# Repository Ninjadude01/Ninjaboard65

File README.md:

# Ninjaboard65

The Ninjaboard65 is a 65% custom keyboard with a knob! Features include hot-swappable gateron yellow switches, pbt double-shot keycaps, and a 3d printed case + plate. It uses qmk firmware, which is fully customizable so you can assign each key to whatever function you want. I decided to build this project as I love hardware and am already familiar with the basics. I wanted a project that would challenge me, which is why I decided to make my own keyboard. Another reason why is because I love playing video games in my free time, so being able to create my very own input device means alot to me, and would be very useful as I can customize it specifically to meet my gaming needs.

Youtube Video Link: https://www.youtube.com/watch?v=n-olJ9K8aAI

# Zine!
.png)

# IRL Photos vs the 3D Renders

<br>
<br>
<br>

<br>
<br>
<br>

# Layout 
I chose a 65% layout as I like to game in my freetime, and this layout is a perfect mix between everyday functionality while still being small and compact.

# Schematic
I designed the Schematic and PCB in Kicad, and chose to use a raspberry pi pico because it has many GPIO pins, making it perfect for my project as I needed 22 pins for my matrix + rotary encoder to work.

# PCB
I am very proud of my clean wiring, as it took me countless hours and I re-did it many times. I also added some cool designs to the backside silkscreen to add some unique flair to my project!

# Case
My keyboard case was created in fusion, and comes in 3 parts. The main part of the case is the base, and has 3 small PCB supports located near the centre left, centre right, and spacebar area. It will have 5 m2 heatset inserts located around the edge of the base. 

My case uses 5 m2 4mm screws that will screw from the top plate into the base. 

The final part of my case is the pico cover, which covers the microcontroller. It connects to the plate through a snap-fit type mechanism (theres an extruded outline on the plate, and an indented section on the underside of the cover.)

# Assembly Guide 
1. Solder the 1N4148 and Kailh hot-swap sockets to the underside of the pcb.
2. Attach and mount the stabilizers, and solder the rotary encoder onto the pcb (facing upwards).
3. Grab all the Gateron Switches and snap them onto the plate, and flip the plate upside down. 
4. Now, with the plate and your pcb facing downwards, slowly lower the pcb into the plate until all the switches have entered their sockets. 
5. Use a soldering iron to heat up the m2 heatset inserts, and push them into the 5 designated holes in the walls of the base case. 
7. Flip your plate attached the the pcb over, and lower it into the base case.
8. Screw the m2 screws into the holes, cover the open Raspberry Pi Pico with the nameplate (optional), and place the keycaps onto the respective keys.
9. All thats left to do now is to flash your Ninjaboard65!

# Firmware Flashing Steps
1. Download the .uf2 file found in the Firmware Folder.
2. Hold down the BOOTSEL button found on the Pico, and connect it back into your device using a usb cable while holding it.
3. A usb drive called RPI-RP2 will appear on your computer.
4. Drag and drop the .uf2 file onto the drive. 
5. The Pico will automatically reboot and you should be good to go.
6. Enjoy your new Ninjaboard65!

# BOM

|Item|Part Name         |Quantity|Description                    |Cost (USD)|Link                                                                                                                                                                                                                                                                                                                                                                                                                                                                                                                                                                                                                                                                                                                                                                                         |
|----|------------------|--------|-------------------------------|----------|---------------------------------------------------------------------------------------------------------------------------------------------------------------------------------------------------------------------------------------------------------------------------------------------------------------------------------------------------------------------------------------------------------------------------------------------------------------------------------------------------------------------------------------------------------------------------------------------------------------------------------------------------------------------------------------------------------------------------------------------------------------------------------------------|
|1   |Custom PCB        |5       |Printed Circut Board           |$20       |https://jlcpcb.com/                                                                                                                                                                                                                                                                                                                                                                                                                                                                                                                                                                                                                                                                                                                                                                          |
|2   |Kb Switches       |110     |Input                          |$32.05    |https://www.aliexpress.com/item/1005008397216226.html?spm=a2g0o.order_list.order_list_main.28.6a7d1802895Pzz                                                                                                                                                                                                                                                                                                                                                                                                                                                                                                                                                                                                                                                                                 |
|3   |Keycaps (Blue)    |133     |Protection                     |$13.64    |https://www.aliexpress.com/item/1005009580866548.html?spm=a2g0o.order_list.order_list_main.17.6a7d1802895Pzz#nav-specification                                                                                                                                                                                                                                                                                                                                                                                                                                                                                                                                                                                                                                                               |
|4   |Hot-swap Sockets  |110     |Allows hot-swapping of switches|$9.88     |https://www.aliexpress.com/item/1005007232040760.html?spm=a2g0o.order_list.order_list_main.5.6a7d1802895Pzz                                                                                                                                                                                                                                                                                                                                                                                                                                                                                                                                                                                                                                                                                  |
|5   |Rotary Encoder    |1       |You can rotate it              |$3.50     |https://www.digikey.ca/en/products/detail/alps-alpine/EC11E15244B2/19529170                                                                                                                                                                                                                                                                                                                                                                                                                                                                                                                                                                                                                                                                                                                  |
|6   |Encoder Knob cap  |1       |Protection                     |$4.25     |https://www.aliexpress.com/item/1005006531154080.html?spm=a2g0o.order_list.order_list_main.5.256d1802T4w9tK                                                                                                                                                                                                                                                                                                                                                                                                                                                                                                                                                                                                                                                                                  |
|7   |Raspberry pi pico |1       |Microcontroller                |$2.89     |https://www.digikey.ca/en/products/detail/raspberry-pi/SC0915/13684020                                                                                                                                                                                                                                                                                                                                                                                                                                                                                                                                                                                                                                                                                                                       |
|8   |Stabilizers       |8       |Increase steadiness of keys    |$7.86     |https://www.aliexpress.com/item/1005007236845004.html?spm=a2g0o.cart.0.0.722238daCCs9vH&mp=1&pdp_npi=6%40dis%21CAD%21CAD%2010.78%21CAD%2010.78%21%21CAD%2010.78%21%21%21%40210328c017745464960958122e1f40%2112000039909995531%21ct%21CA%217451194651%21%211%210%21                                                                                                                                                                                                                                                                                                                                                                                                                                                                                                                           |
|9   |Rubber Bumpers    |10      |Prevent sliding                |$3.78     |https://www.aliexpress.com/item/1005003881918836.html?spm=a2g0o.productlist.main.26.276a2cb9RSUSKP&algo_pvid=2cb2056c-1932-4d95-a10e-0f118e3ed9cb&algo_exp_id=2cb2056c-1932-4d95-a10e-0f118e3ed9cb-25&pdp                                                                                                                                                                                                                                                                                                                                                                                                                                                                                                                                                                                    |
|10  |M2 Heatset Inserts|100     |Threaded metal hole for screws |$5.76     |https://www.aliexpress.com/item/1005006838108683.html?spm=a2g0o.cart.0.0.1c1b38dalGfMuU&mp=1&pdp_npi=6%40dis%21CAD%21CAD%205.20%21CAD%205.20%21%21CAD%205.20%21%21%21%4021033d9d17760010503013922ef23d%2112000038467725083%21ct%21CA%217451194651%21%211%210%21                                                                                                                                                                                                                                                                                                                                                                                                                                                                                                                              |
|11  |M2 Screw 4mm      |50      |Screw                          |$1.70     |https://www.aliexpress.com/item/32973784147.html?spm=a2g0o.productlist.main.1.304apnmvpnmvhX&algo_pvid=8e4bcfb2-c0a1-48f2-ad5e-84593aa7934a&algo_exp_id=8e4bcfb2-c0a1-48f2-ad5e-84593aa7934a-0&pdp_ext_f=%7B%22order%22%3A%227855%22%2C%22spu_best_type%22%3A%22price%22%2C%22eval%22%3A%221%22%2C%22fromPage%22%3A%22search%22%7D&pdp_npi=6%40dis%21CAD%212.26%212.26%21%21%211.60%211.60%21%402101e2b417760020144634724ef5ec%2112000024189797294%21sea%21CA%217451194651%21X%211%210%21n_tag%3A-29912%3Bd%3A8fd05d1b%3Bm03_new_user%3A-29895&curPageLogUid=kvh1vbqAtJaq&utparam-url=scene%3Asearch%7Cquery_from%3A%7Cx_object_id%3A32973784147%7C_p_origin_prod%3A                                                                                                                         |
|12  |1N4148 Diodes     |100     |Prevent kb switch ghosting     |$1.73     |https://www.aliexpress.com/item/1005004962400215.html?spm=a2g0o.productlist.main.8.314c7Zzp7Zzp1O&aem_p4p_detail=202604120710367250743856096580001658181&algo_pvid=9a5c0ddc-1bdb-4d52-bd69-b6aeb1a7dc6b&algo_exp_id=9a5c0ddc-1bdb-4d52-bd69-b6aeb1a7dc6b-7&pdp_ext_f=%7B%22order%22%3A%222280%22%2C%22spu_best_type%22%3A%22price%22%2C%22eval%22%3A%221%22%2C%22fromPage%22%3A%22search%22%7D&pdp_npi=6%40dis%21CAD%212.39%212.39%21%21%211.69%211.69%21%402101e83017760030363003545e4ed8%2112000031168735020%21sea%21CA%217451194651%21X%211%210%21n_tag%3A-29912%3Bd%3A8fd05d1b%3Bm03_new_user%3A-29895&curPageLogUid=O5tBJUtwCY0i&utparam-url=scene%3Asearch%7Cquery_from%3A%7Cx_object_id%3A1005004962400215%7C_p_origin_prod%3A&search_p4p_id=202604120710367250743856096580001658181_4|
|    |                  |        |Total Cost                     |$107.04   |                                                                                                                                                                                                                                                                                                                                                                                                                                                                                                                                                                                                                                                                                                                                                                                             |

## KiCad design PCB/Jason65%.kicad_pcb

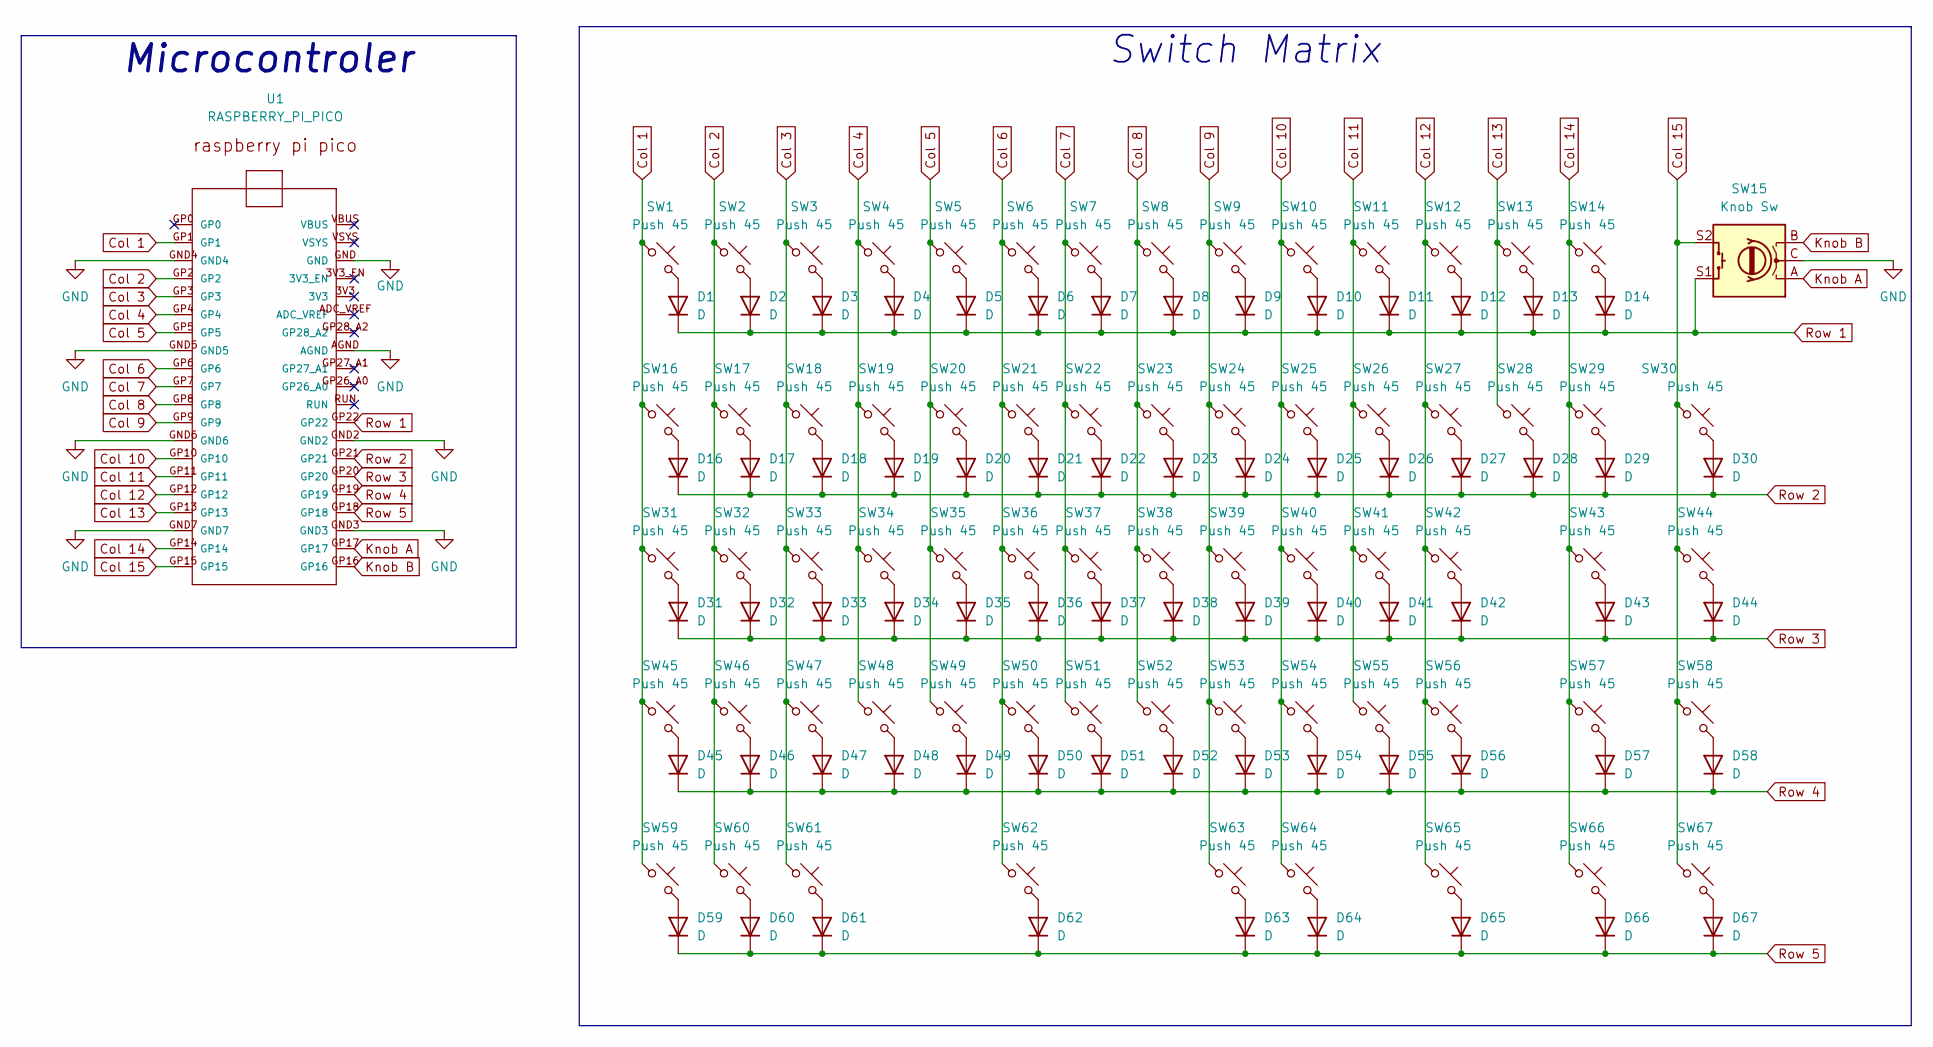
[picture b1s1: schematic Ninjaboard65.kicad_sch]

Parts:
D1, D2, D3, D4, D5, D6, D7, D8, D9, D10, D11, D12, D13, D14, D16, D17, D18, D19, D20, D21, D22, D23, D24, D25, D26, D27, D28, D29, D30, D31, D32, D33, D34, D35, D36, D37, D38, D39, D40, D41, D42, D43, D44, D45, D46, D47, D48, D49, D50, D51, D52, D53, D54, D55, D56, D57, D58, D59, D60, D61, D62, D63, D64, D65, D66, D67: D; D_DO-35_SOD27_P7.62mm_Horizontal
SW1, SW2, SW3, SW4, SW5, SW6, SW7, SW8, SW9, SW10, SW11, SW12, SW13, SW17, SW18, SW19, SW20, SW21, SW22, SW23, SW24, SW25, SW26, SW27, SW28, SW30, SW32, SW33, SW34, SW35, SW36, SW37, SW38, SW39, SW40, SW41, SW42, SW44, SW46, SW47, SW48, SW49, SW50, SW51, SW52, SW53, SW54, SW55, SW57, SW58, SW65, SW66, SW67: Push 45; bluesw
SW14: Push 45; SW_Hotswap_Kailh_MX_Plated_2.00u
SW15: Knob Sw; RotaryEncoder_Alps_EC11E-Switch_Vertical_H20mm
SW16, SW29: Push 45; SW_Hotswap_Kailh_MX_Plated_1.50u
SW31, SW56: Push 45; SW_Hotswap_Kailh_MX_Plated_1.75u
SW43, SW45: Push 45; SW_Hotswap_Kailh_MX_Plated_2.25u
SW59, SW60, SW61, SW63, SW64: Push 45; SW_Hotswap_Kailh_MX_Plated_1.25u
SW62: Push 45; SW_Hotswap_Kailh_MX_Plated_6.25u
U1: RASPBERRY_PI_PICO

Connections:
Col 1: SW1.1, SW16.1, SW31.1, SW45.1, SW59.1, U1.GP1
Col 2: SW2.1, SW17.1, SW32.1, SW46.1, SW60.1, U1.GP2
Col 3: SW3.1, SW18.1, SW33.1, SW47.1, SW61.1, U1.GP3
Col 4: SW4.1, SW19.1, SW34.1, SW48.1, U1.GP4
Col 5: SW5.1, SW20.1, SW35.1, SW49.1, U1.GP5
Col 6: SW6.1, SW21.1, SW36.1, SW50.1, SW62.1, U1.GP6
Col 7: SW7.1, SW22.1, SW37.1, SW51.1, U1.GP7
Col 8: SW8.1, SW23.1, SW38.1, SW52.1, U1.GP8
Col 9: SW9.1, SW24.1, SW39.1, SW53.1, SW63.1, U1.GP9
Col 10: SW10.1, SW25.1, SW40.1, SW54.1, SW64.1, U1.GP10
Col 11: SW11.1, SW26.1, SW41.1, SW55.1, U1.GP11
Col 12: SW12.1, SW27.1, SW42.1, SW56.1, SW65.1, U1.GP12
Col 13: SW13.1, SW28.1, U1.GP13
Col 14: SW14.1, SW29.1, SW43.1, SW57.1, SW66.1, U1.GP14
Col 15: SW15.S2, SW30.1, SW44.1, SW58.1, SW67.1, U1.GP15
GND: SW15.C, U1.AGND, U1.GND, U1.GND2, U1.GND3, U1.GND4, U1.GND5, U1.GND6, U1.GND7
Knob A: SW15.A, U1.GP17
Knob B: SW15.B, U1.GP16
unnamed: D1.2 (A), SW1.2
unnamed: D2.2 (A), SW2.2
unnamed: D3.2 (A), SW3.2
unnamed: D4.2 (A), SW4.2
unnamed: D5.2 (A), SW5.2
unnamed: D6.2 (A), SW6.2
unnamed: D7.2 (A), SW7.2
unnamed: D8.2 (A), SW8.2
unnamed: D9.2 (A), SW9.2
unnamed: D10.2 (A), SW10.2
unnamed: D11.2 (A), SW11.2
unnamed: D12.2 (A), SW12.2
unnamed: D13.2 (A), SW13.2
unnamed: D14.2 (A), SW14.2
unnamed: D16.2 (A), SW16.2
unnamed: D17.2 (A), SW17.2
unnamed: D18.2 (A), SW18.2
unnamed: D19.2 (A), SW19.2
unnamed: D20.2 (A), SW20.2
unnamed: D21.2 (A), SW21.2
unnamed: D22.2 (A), SW22.2
unnamed: D23.2 (A), SW23.2
unnamed: D24.2 (A), SW24.2
unnamed: D25.2 (A), SW25.2
unnamed: D26.2 (A), SW26.2
unnamed: D27.2 (A), SW27.2
unnamed: D28.2 (A), SW28.2
unnamed: D29.2 (A), SW29.2
unnamed: D30.2 (A), SW30.2
unnamed: D31.2 (A), SW31.2
unnamed: D32.2 (A), SW32.2
unnamed: D33.2 (A), SW33.2
unnamed: D34.2 (A), SW34.2
unnamed: D35.2 (A), SW35.2
unnamed: D36.2 (A), SW36.2
unnamed: D37.2 (A), SW37.2
unnamed: D38.2 (A), SW38.2
unnamed: D39.2 (A), SW39.2
unnamed: D40.2 (A), SW40.2
unnamed: D41.2 (A), SW41.2
unnamed: D42.2 (A), SW42.2
unnamed: D43.2 (A), SW43.2
unnamed: D44.2 (A), SW44.2
unnamed: D45.2 (A), SW45.2
unnamed: D46.2 (A), SW46.2
unnamed: D47.2 (A), SW47.2
unnamed: D48.2 (A), SW48.2
unnamed: D49.2 (A), SW49.2
unnamed: D50.2 (A), SW50.2
unnamed: D51.2 (A), SW51.2
unnamed: D52.2 (A), SW52.2
unnamed: D53.2 (A), SW53.2
unnamed: D54.2 (A), SW54.2
unnamed: D55.2 (A), SW55.2
unnamed: D56.2 (A), SW56.2
unnamed: D57.2 (A), SW57.2
unnamed: D58.2 (A), SW58.2
unnamed: D59.2 (A), SW59.2
unnamed: D60.2 (A), SW60.2
unnamed: D61.2 (A), SW61.2
unnamed: D62.2 (A), SW62.2
unnamed: D63.2 (A), SW63.2
unnamed: D64.2 (A), SW64.2
unnamed: D65.2 (A), SW65.2
unnamed: D66.2 (A), SW66.2
unnamed: D67.2 (A), SW67.2
Row 1: D1.1 (K), D2.1 (K), D3.1 (K), D4.1 (K), D5.1 (K), D6.1 (K), D7.1 (K), D8.1 (K), D9.1 (K), D10.1 (K), D11.1 (K), D12.1 (K), D13.1 (K), D14.1 (K), SW15.S1, U1.GP22
Row 2: D16.1 (K), D17.1 (K), D18.1 (K), D19.1 (K), D20.1 (K), D21.1 (K), D22.1 (K), D23.1 (K), D24.1 (K), D25.1 (K), D26.1 (K), D27.1 (K), D28.1 (K), D29.1 (K), D30.1 (K), U1.GP21
Row 3: D31.1 (K), D32.1 (K), D33.1 (K), D34.1 (K), D35.1 (K), D36.1 (K), D37.1 (K), D38.1 (K), D39.1 (K), D40.1 (K), D41.1 (K), D42.1 (K), D43.1 (K), D44.1 (K), U1.GP20
Row 4: D45.1 (K), D46.1 (K), D47.1 (K), D48.1 (K), D49.1 (K), D50.1 (K), D51.1 (K), D52.1 (K), D53.1 (K), D54.1 (K), D55.1 (K), D56.1 (K), D57.1 (K), D58.1 (K), U1.GP19
Row 5: D59.1 (K), D60.1 (K), D61.1 (K), D62.1 (K), D63.1 (K), D64.1 (K), D65.1 (K), D66.1 (K), D67.1 (K), U1.GP18

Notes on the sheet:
Microcontroler
Switch Matrix

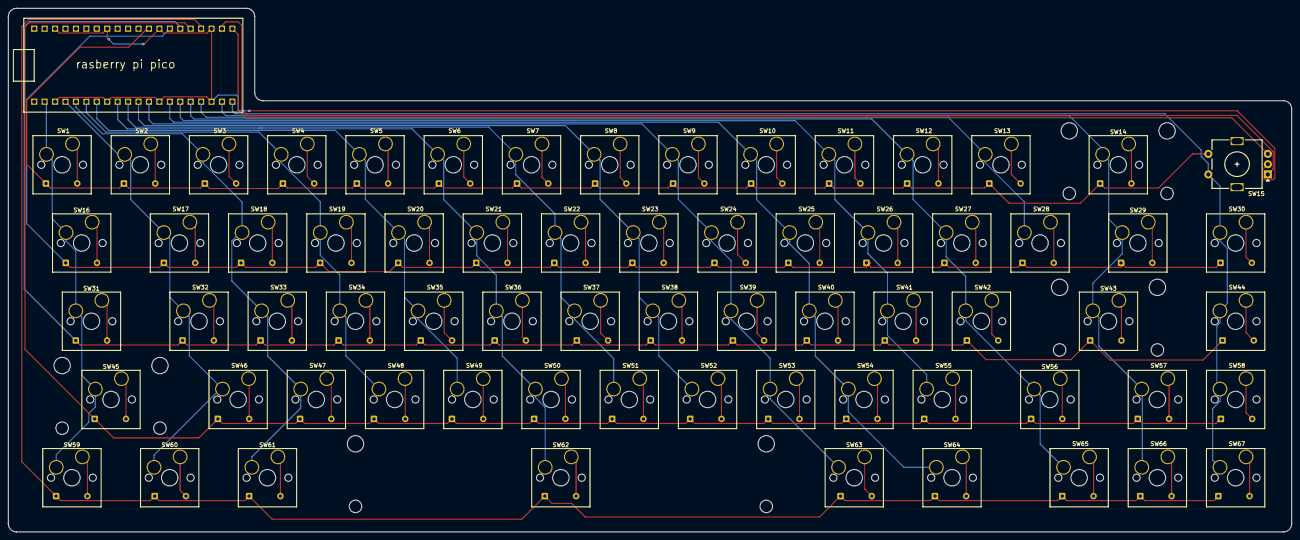
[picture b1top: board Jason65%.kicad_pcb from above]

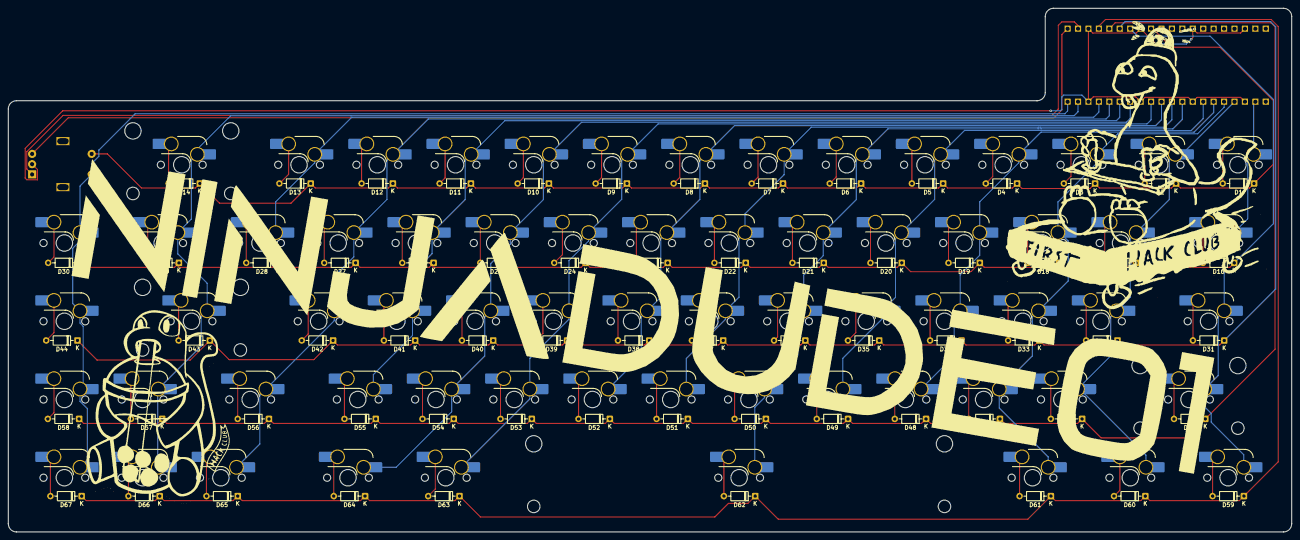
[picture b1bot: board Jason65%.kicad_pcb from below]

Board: 2 copper layers, 312.5 x 127.5 mm, 134 parts (66 on the bottom side), 89 nets.

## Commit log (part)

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2026-04-08 Create temp
2026-04-12 Rename temp to temp
2026-04-12 Added CAD files
2026-04-12 Rename Ninjaboard65.f3z to CAD/Ninjaboard65.f3z
2026-04-12 Rename Ninjaboard65.step to CAD/Ninjaboard65.step
2026-04-12 Rename Jason65%.kicad_pcb to Ninjaboard65.kicad_pcb
2026-04-12 Rename Jason65%.kicad_sch to Ninjaboard65.kicad_sch
2026-04-12 Rename Jason65%.kicad_pro to Ninjaboard65.kicad_pro
2026-04-18 test
2026-04-18 Fusion Files
2026-04-18 Step Files
2026-04-18 Create tempo
2026-04-18 Fixed Issue
2026-04-18 Rename Ninjaboard65%-BOM.csv to Ninjaboard65-BOM.csv
2026-04-20 Rename Ninjaboard65-BOM.csv to Assets/Ninjaboard65-BOM.csv
2026-04-20 Rename Ninjaboard65-Fallout-Zine.png to Assets/Ninjaboard65-Fallout-Zine.png
2026-04-20 Rename Ninjaboard65-Layout.json to Assets/Ninjaboard65-Layout.json
2026-04-27 Create temno
2026-04-27 added step file
2026-06-17 Rename 65% Keeb + Knob! (IRL).png to Ninjaboard65-(ZINE_IRL).png
